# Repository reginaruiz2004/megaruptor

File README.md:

# Megaruptor

An open-source, low-cost DNA shearing device built on the [Poseidon syringe pump](https://github.com/machineagency/poseidon) platform — designed as an accessible alternative to commercial mechanical shearing instruments (e.g., Diagenode Megaruptor 3) for genomic library preparation workflows, particularly long-read sequencing (Oxford Nanopore).

> **Status:** 🚧 In progress

---

## Overview

Mechanical DNA shearing instruments are a common bottleneck in labs working with long-read sequencing platforms, both in cost and accessibility. This project adapts the open-source Poseidon syringe pump design to build a functional, hackable shearing device using off-the-shelf electronics, 3D-printed parts, and standard insulin syringes as the shearing element.

The goal is a device that is:
- **Low-cost** — built from widely available components
- **Reproducible** — fully documented, open hardware
- **Hackable** — easy to modify shear force/speed parameters for different fragment size targets

---

## How It Works

DNA is sheared by repeatedly forcing a sample through a narrow-gauge needle at controlled speed, using a syringe pump mechanism driven by a stepper motor. Shear force and fragment size distribution are governed by needle gauge, plunger speed, and number of passes.

---

## Bill of Materials (Key Components)

| Component | Spec / Notes |
|---|---|
| Shearing element | BD Ultra-Fine 0.3 mL, 31G insulin syringes |
| Stepper motor | NEMA 17 |
| Motor driver | A4988 |
| Controller | CNC Shield V3 + Arduino Uno R3 |
| Safety | Mechanical limit switch (NC, fail-safe primary) + current sensing (secondary) |
| Frame/structural parts | 3D-printed (PLA), based on Poseidon design |

Full BOM with vendor links: [`docs/BOM.md`](docs/BOM.md) *(coming soon)*

---

## 3D Printed Parts

This build uses 4 standard components from the original Poseidon design, plus 2 custom parts designed for this build:

| Part | Type | Notes |
|---|---|---|
| Poseidon base/frame components (×4) | Standard | From original Poseidon design |
| Sleeve adapter | Custom | OD 8 mm, ID 6.1 mm, 30 mm length |
| Eppendorf bracket | Custom | 45° angle mount |

All STL files are available in [`/STL`](./STL). Source CAD files (where available) are in [`/CAD`](./CAD).

---

## Repository Structure

```
megaruptor/
├── README.md
├── STL/                  # Printable 3D files
├── CAD/                  # Source CAD files (Fusion 360 / FreeCAD)
├── firmware/             # Arduino control code
├── docs/
│   ├── BOM.md            # Full bill of materials with vendors/costs
│   ├── DECISIONS.md      # Design decisions & rationale
│   ├── ASSEMBLY.md       # Build/assembly instructions
│   └── images/           # Build photos
```

---

## Design Decisions

Key engineering choices and their rationale are documented in [`docs/DECISIONS.md`](docs/DECISIONS.md), including:
- Hybrid safety design (mechanical limit switch + current sensing) over software-only stall detection
- Choice of insulin syringe gauge for shearing element
- Custom part tolerances (e.g., sleeve adapter fit)

---

## Build Progress

- [x] Source components (NEMA 17, A4988, Arduino Uno R3, syringes)
- [x] Design custom parts (sleeve adapter, Eppendorf bracket)
- [x] 3D print all components
- [x] Full mechanical assembly
- [ ] Firmware integration and motor control testing
- [ ] Validation with real DNA samples (fragment size distribution vs. commercial shearing)

---

## Progress Log

### July 21 2026
Mechanical assembly in progress. Key steps completed this round:

- Drilled out the rod holes on the 3D-printed PLA parts to fit the guide rods — the as-printed tolerances were too tight, so holes were carefully widened with a drill bit until the rods slid through smoothly.
- Installed screws on all designated screw holes across the printed parts to secure the frame.
- Threaded the brass (gold) lead screw nut onto the central leadscrew and secured it inside the carriage's nut trap with M3 screws, so it stays anti-rotated — this is what converts the leadscrew's rotation into linear motion, pulling the carriage along the two guide rods instead of just spinning freely with the screw.
- Mounted the carriage onto the guide rods and confirmed it slides smoothly along the full travel range by turning the leadscrew by hand.

📹 [Watch the assembly video](docs/images/progreso_julio2026/video1.mp4)

### July 27, 2026

**A4988 Driver Calibration — Complete**

Key steps completed this round:

- Installed jumper headers at each motor position on the CNC shield to configure 1/2-step mode.
- Seated all four A4988 drivers into their respective positions on the CNC shield (X, Y, Z, and A axes).
- Mounted the CNC shield onto the Arduino UNO.
- Calibrated each A4988 driver to a reference voltage of 0.96V using a digital multimeter, with the negative probe on the CNC shield's GND pin and the positive probe used to measure the potentiometer during adjustment. This value was derived from: Vref = Imax × (8 × Rsense) = 1.2A × (8 × 0.1Ω) = 0.96V.
- Voltage adjustments were made by turning each driver's onboard potentiometer with a small screwdriver while simultaneously monitoring voltage with the multimeter's positive probe.
- Once all four drivers were calibrated to 0.96V, proceeded to connect the NEMA 17 stepper motor.
- **Note:** Many NEMA 17 motors ship with connectors where the wire color order differs between the motor and driver ends. This was the case here — the pin order did not match. To correct it, I released the terminals from the connector housing using a small screwdriver and reseated them in the correct sequence.
- Connected the NEMA 17 motor to the CNC shield via the X-axis A4988 driver.
- Stripped two jumper wires and connected them to the CNC shield's positive (+) and negative (–) power terminals to interface with the barrel jack adapter.

### August 3, 2026

**NEMA 17 setup completed**

Key steps completed this round:

- Installed the NEMA17 into the megaruptor base support. Removed awkwardness when the NEMA17 motor turns on.
- Switched the main central screw to a smaller length one so it can all properly fit with now the NEMA17 closer to the whole device.
- I started having an issue with one of the rods whenever the cart moved forwards and backwards. The rod would also move with the cart's movements. To fix this, I setup longer screws in the base so that they would hold the rods in place without worry of any movement when the cart would begin to do its job.
- Completed a design of 3d printed case for the CNC shield and arduino. There are 5 openings in the case: Arduino USB cable, Jack Barrel power source for Arduino, On/Off switch, cart switch, and an opening for the NEMA 17 wires.

### August 4, 2026

**3D Printed Case**

Key steps completed this round:

- I 3d printed the case for the electrical components.
- Switch assembly: On/Off switch, forwards/backwards switch that controls the cart movement

### August 5, 2026

**Complete setup of megaruptor**

Key steps completed this round:

- Connected the switch that moves the cart forwards and backwards. I connected it directly to the CNC shield instead of the Arduino. Why? Because all of the pins from the arduino are taken by the CNC shield since it is stacked. Therefore, there are pins in the CNC shield that are available to act as digital pins. (Y+ and Z- were used in this case)
- Connected the on and off switch with the following circuit. Terminal 1 (LED) was connected to the gnd of the CNC shield. There was also a wire from CNC shield GND soldered to the Arduino GND pin of the jack barrel connector. Then Terminal 2 (common) was connected to the + of the CNC shield. And then terminal 3 of the switch was soldered to the + pin of the jack barrel terminal. Therefore, when you connect the jack barrel connector to the arduino, voltage has to first go through the switch before reaching the CNC shield.
- After setting up all the necessary switches, it was time to set it up with the case. The switches went into their designated spots in the case and a zip tie was used to organize all loose wires. I plan to add magnets to the back of the NEMA17 and the case so the whole machine can be in one piece rather than two separate pieces.

---

## Acknowledgments

This project builds on the open-source [Poseidon](https://github.com/machineagency/poseidon) syringe pump platform. Full credit to the original design team for the foundational mechanical design this project adapts.

---

## License

*(To be determined — consider MIT for firmware/code and CC-BY or CC-BY-SA for hardware designs)*

---

## Author

**Regina Ruiz** — Bioinformatics / Lab Sciences, Granatum Bioworks
[GitHub](https://github.com/reginaruizb)

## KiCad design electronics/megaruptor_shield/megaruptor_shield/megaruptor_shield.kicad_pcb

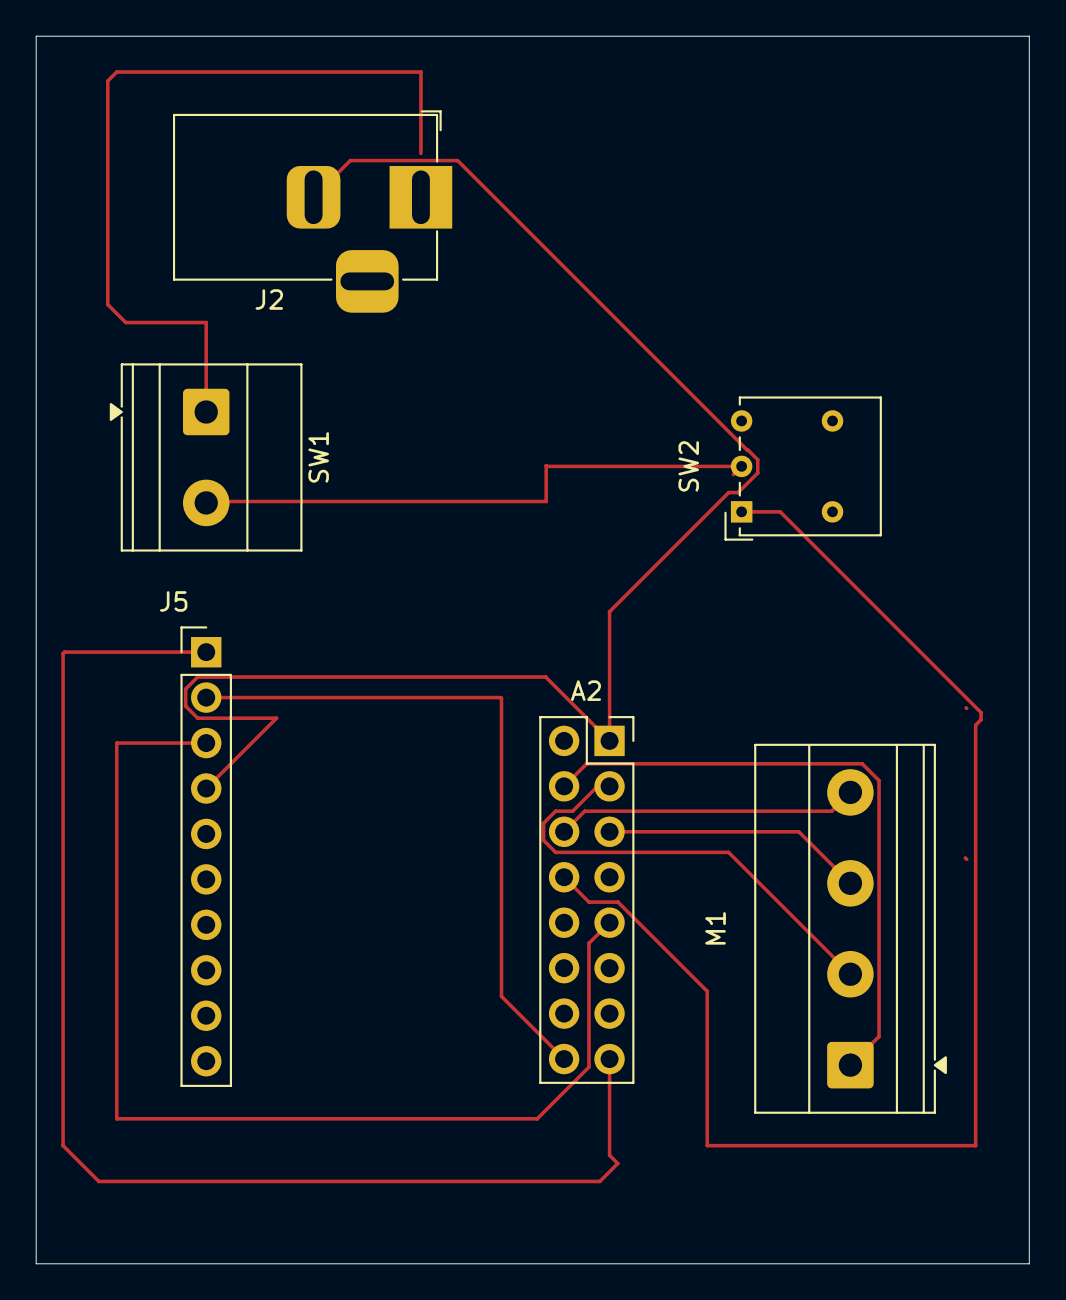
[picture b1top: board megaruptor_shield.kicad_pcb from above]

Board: 2 copper layers, 55.5 x 68.6 mm, 6 parts (0 on the bottom side), 11 nets.

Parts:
A2: Pololu_Breakout_A4988; PinSocket_2x08_P2.54mm_Vertical
J2: Barrel_Jack; BarrelJack_Horizontal
J5: Conn_01x10; PinHeader_1x10_P2.54mm_Vertical
M1: Stepper_Motor_bipolar; TerminalBlock_Phoenix_MKDS-1,5-4-5.08_1x04_P5.08mm_Horizont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
SW1: SW_Push; TerminalBlock_Phoenix_MKDS-1,5-2-5.08_1x02_P5.08mm_Horizont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
SW2: SW_SPDT; SW_Lever_1P2T_NKK_GW12LxH

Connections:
+12V: J2.1, SW1.1
/DIR: A2.16 (DIR), J5.2 (D5)
/ENABLE: A2.9 (~ENABLE), J5.3 (D8)
/GND: A2.1 (GND), J2.2, J5.4 (GND)
/STEP: A2.15 (STEP), J5.1 (D2)
unnamed: A2.4 (1A), M1.1
unnamed: A2.3 (1B), M1.2 (-_2)
unnamed: A2.5 (2A), M1.3
unnamed: A2.6 (2B), M1.4
unnamed: A2.8 (VMOT), SW2.1 (A)
unnamed: SW1.2, SW2.2 (B)
